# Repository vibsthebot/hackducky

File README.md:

# HackDucky - New YSWS!

The hackclub themed USB rubber ducky ! - Check out [hackducky](https://hackclub.slack.com/archives/C08B8HZBC85)

# What is this?

Hackducky is hackclubs own version of making a USB rubber ducky built by hackclubers.A usb rubber ducky is basically something that looks like a USB but is actually a trojan. It pretends to be a keyboard to the computer allowing you to basically take control of the computer you plug it into

## What you get

- Hackducky Board
    -  Dual USB ports (USB-A and USB-C)
    -  LED for the status - you can use it for other things if you like !
    -  Button for any extra features you may want to add !
    -  All duckyscripts are stored in the Hackduckys flash memory !

## Getting Started

1. - WIP

# Submission Criteria  

## 1. Time Requirement  
- **HackDucky Light:** Minimum of **3-4 hours** of development.  
- **HackDucky Pro:** Minimum of **5-6 hours** of development.  
- **Tracking:** Use **WakaTime** to track your development hours.  

## 2. Core Features (Must have 3)  
- Not just simple actions—core features should be impactful and unique.  
- **Examples:**  
  1. Open Notepad, start typing gibberish, and change the desktop background.  
  2. Open the terminal, run commands, and create pop-ups to scare the user.  
  3. Fake a system crash by downloading a **blue screen image** and freezing the mouse.  

## 3. Additional Features (Must have 5-7)  
- Include **at least 5-7 normal features** outside of the core features.  
- The more features, the better!  

## 4. Originality  
- Your project must be an **original idea** and not a direct copy from a tutorial.  
- Tutorials can be referenced, but your submission should be your own creation.  

## 5. Submission Limit  
- You can submit **multiple projects**, but you can only receive **one HackDucky** (either Pro or Light).  

## What the LED indicators mean

- Triple blink: Startup Sequence
- Single blink: Working/Processing - running/Starting Execution
- Rapid blinking: DuckyScript is incorrect / Firmware broke 😭 - Create a PR or new issue desribing the firmware problem

## Troubleshooting the LED's

1. LED rapidly blinking at startup:
 - Programming Mode
    - All is working great!
    - Its meant to blink rapidly in this mode
 - Payload Mode
       - Something is wrong with your duckyscript
       - Something is wrong with the firmware ( Create an Issue! )

3. Script not running:
   - Check script syntax
   - Verify file is properly saved
   - Try reformatting MicroSD card

4. Keyboard not recognized:
   - Try different USB port
   - Check USB connection
   - Verify target system supports USB HID

## Safety Notes

- pls dont hack people with this pls - its only ethical

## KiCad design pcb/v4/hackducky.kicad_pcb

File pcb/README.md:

# 🦆 HackDucky

HackDucky is a compact, powerful RP2040-based USB device inspired by the concept of a "USB Rubber Ducky" — but fully open-source and customizable. It features dual USB ports (Type-A & Type-C), RGB status indicator, SD card support, and a generous 16MB flash. Ideal for scripting, automation, HID emulation, and more!

## 🔧 Features

* **RP2040 Microcontroller** – Dual-core Arm Cortex-M0+ @ 133MHz
* **16MB Flash** – Plenty of room for Ducky scripts, firmware, and more
* **USB-C & USB-A Ports** – Plug into any host device with ease
* **Micro SD Card Slot** – Store payloads, logs, or configs externally
* **RGB Neopixel** – Visual feedback for status, payload execution, etc
* **Compact Custom PCB** – Designed with portability and DIY hacking in mind

## 🧠 What Can It Do?

* Act as a USB HID device (keyboard/mouse automation)
* Emulate serial or mass storage devices
* Read payloads from SD card and execute them
* Light up RGB based on execution state (idle, running, error)
* Load firmware like CircuitPython, TinyUSB, or custom UF2 payloads

## 💻 Getting Started

1. **Flash Firmware**
   Connect via USB and flash with your favorite firmware (e.g. CircuitPython, Raspberry Pi Pico SDK UF2, etc).

2. **Insert SD Card (Optional)**
   Load your payloads/scripts/configs on a FAT32-formatted card.

3. **Connect to Host via USB-A**
   HackDucky will start executing its payload or HID script automatically (depending on firmware).

4. **RGB Status LED**

## ⚡ Power & USB Notes

* Use **USB-C & USB-A for power and flashing**

## 🧰 Tools Used

* KiCad for PCB Design
* RP2040 SDK / CircuitPython
* Open-source hardware and firmware philosophy

## 📸 Preview
Coming Soon
## 🔐 Disclaimer

This device is for **educational and ethical hacking purposes only**. Use responsibly. The creators is not responsible for any misuse.

---

## 📫 Connect

Built with ❤️ by [Souptik Samanta](https://souptik.me) & [Aarav Jhamb](https://github.com/The-UnknownHacker)

GitHub: [@souptik-samanta](https://github.com/souptik-samanta) & [Aarav Jhamb](https://github.com/The-UnknownHacker)
Instagram: [@souptik.me](https://instagram.com/souptik.me) & [Aarav Jhamb](aaravjhamb.com)
Hack Clubber & Hardware Hacker 💻🔌             Hack Clubber & Ethical Hacker 💻🔌

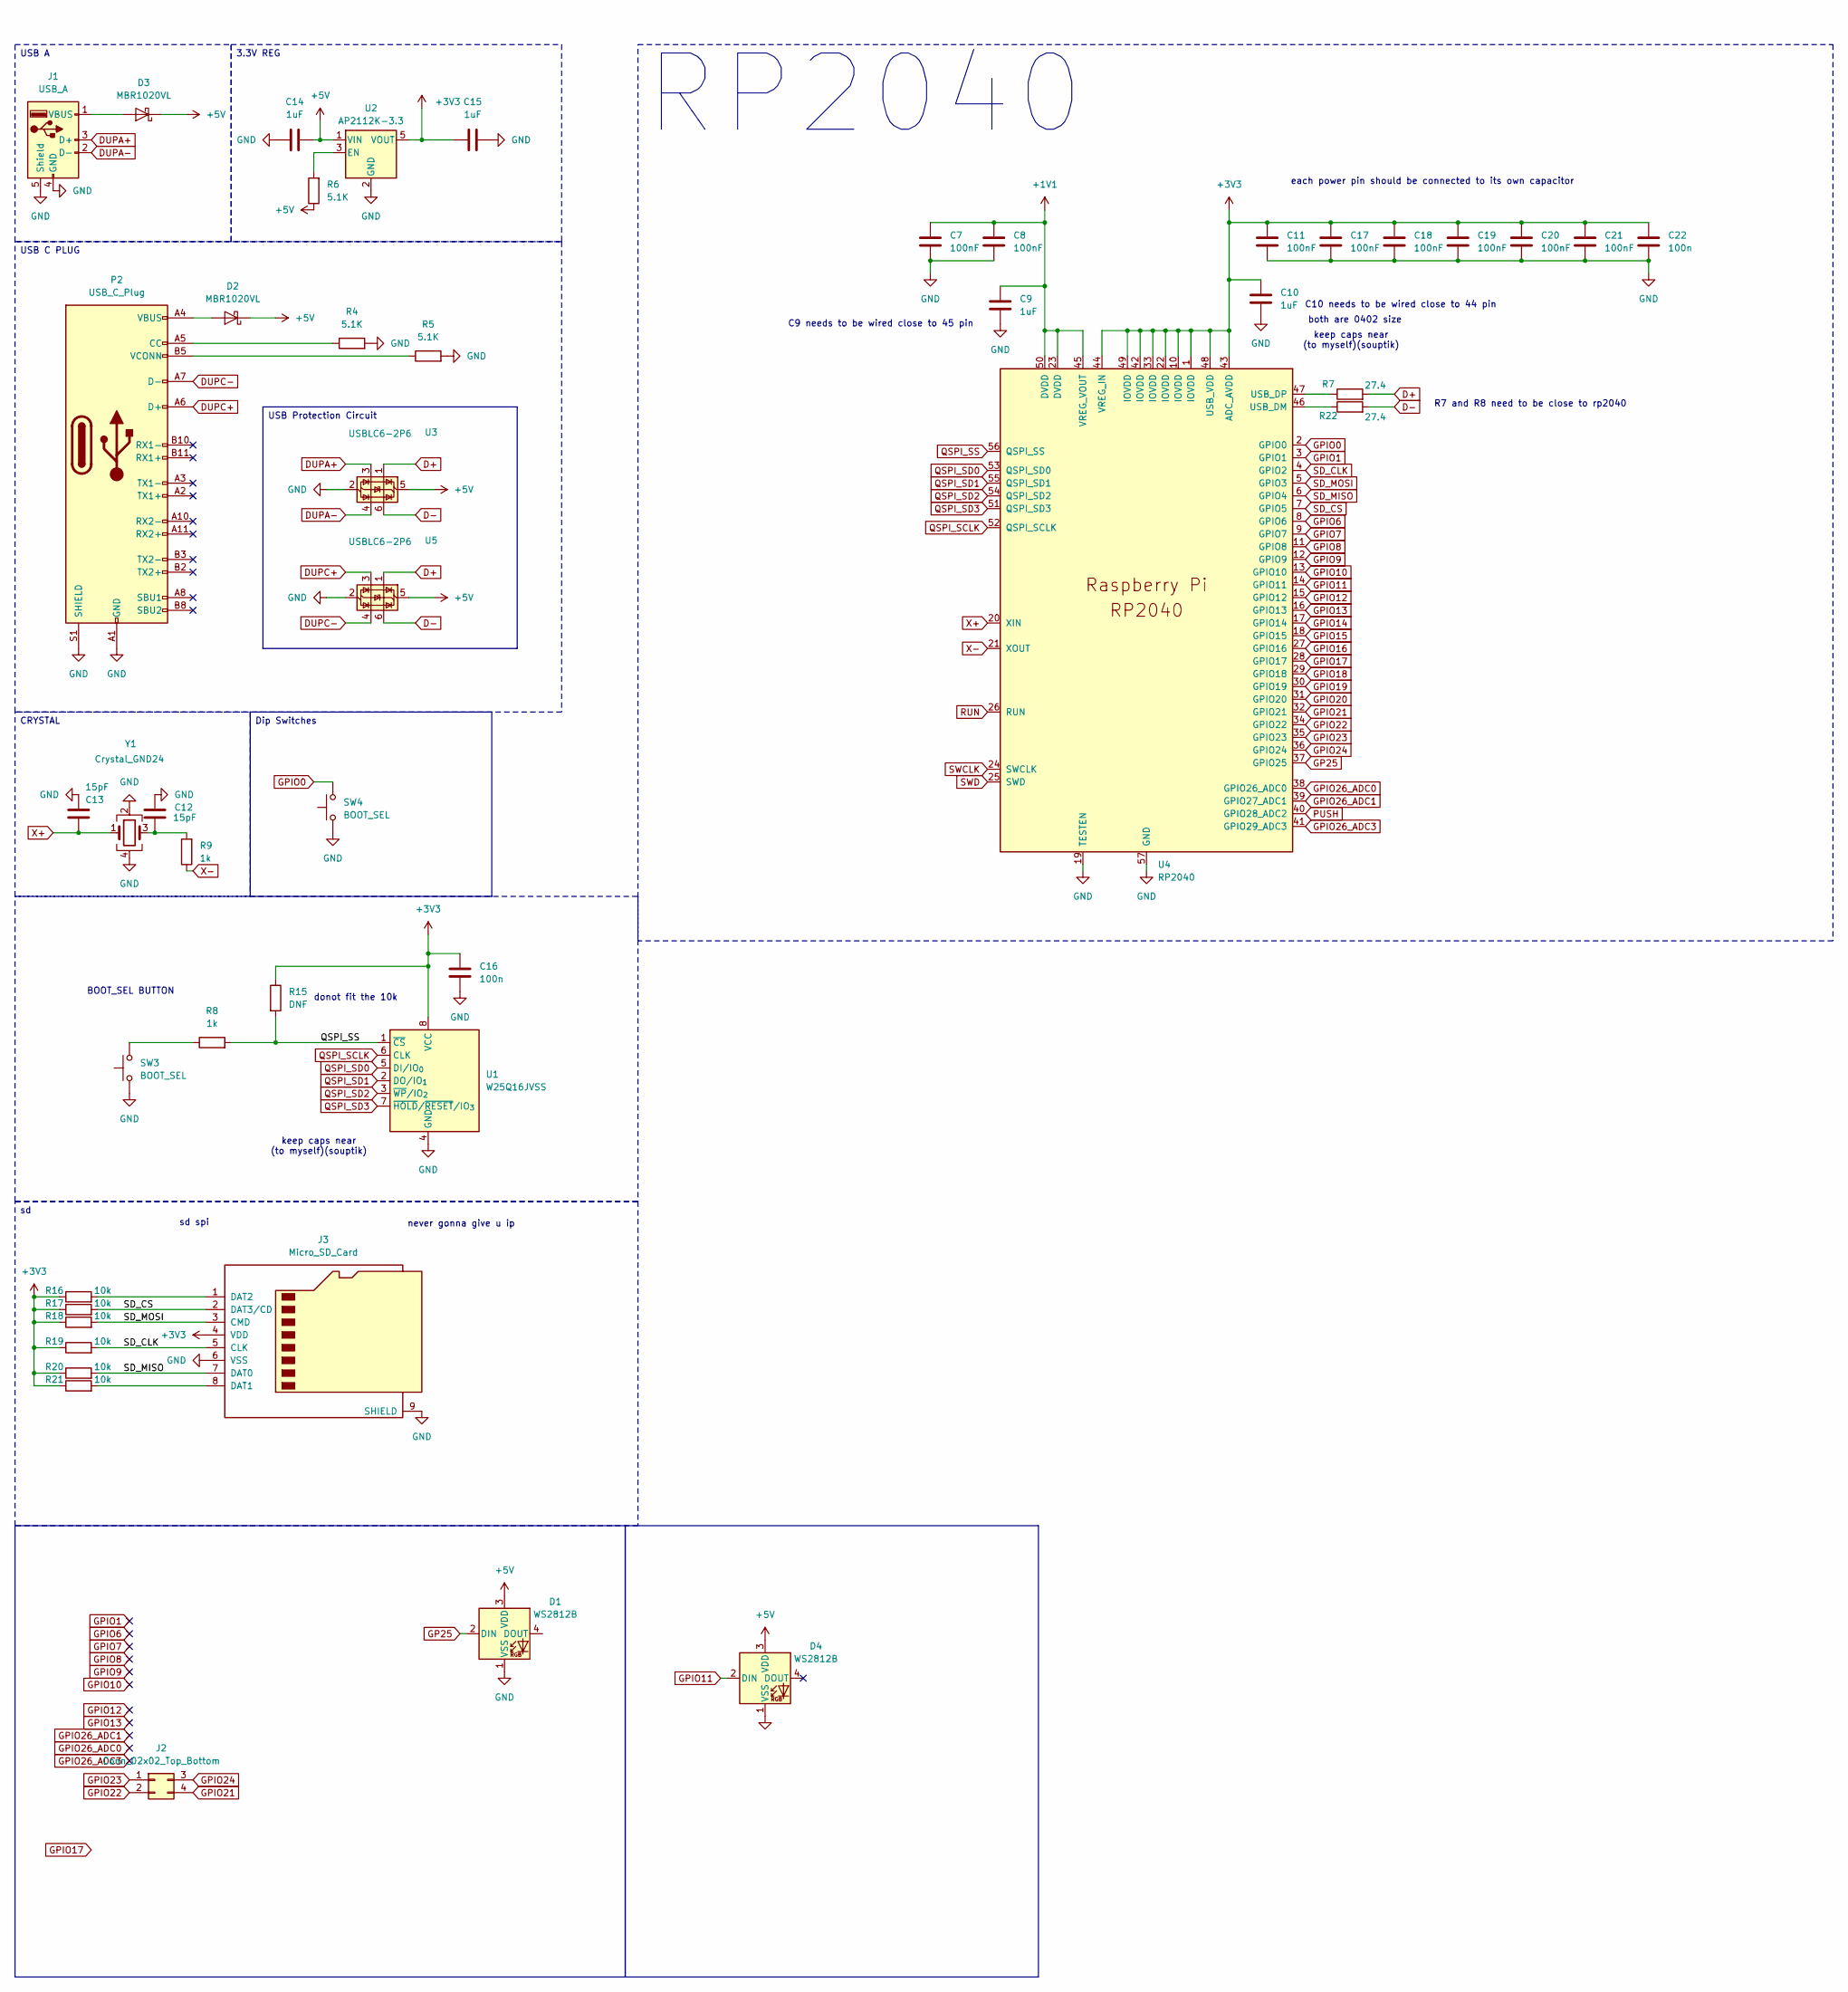
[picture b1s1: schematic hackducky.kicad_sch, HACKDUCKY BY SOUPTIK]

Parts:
C7, C8, C11, C17, C18, C19, C20, C21: 100nF; C_0402_1005Metric
C9, C10, C14: 1uF; C_0402_1005Metric
C12, C13: 15pF; C_0402_1005Metric
C15: 1uF; C_0805_2012Metric
C16, C22: 100n; C_0402_1005Metric
D1, D4: WS2812B; LED_WS2812B-2020_PLCC4_2.0x2.0mm
D2, D3: MBR1020VL; D_SOD-123F
J1: USB_A; USB_A_CNCTech_1001-011-01101_Horizontal
J2: Conn_02x02_Top_Bottom; PinHeader_2x02_P1.00mm_Vertical_SMD
J3: Micro_SD_Card; microSD_HC_Molex_47219-2001
P2: USB_C_Plug; USB_C_Plug_Molex_105444
R4, R5: 5.1K; C_0402_1005Metric
R6: 5.1K; R_0805_2012Metric
R7, R22: 27.4; R_0402_1005Metric
R8, R9: 1k; R_0402_1005Metric
R15: DNF; R_0805_2012Metric_Pad1.20x1.40mm_HandSolder
R16, R17, R18, R19, R20, R21: 10k; R_0402_1005Metric
SW3, SW4: BOOT_SEL; SW_Push_SPST_NO_Alps_SKRK; LCSC C318884
U1: W25Q16JVSS; SOIC-8_5.3x5.3mm_P1.27mm
U2: AP2112K-3.3; SOT-23-5
U3, U5: USBLC6-2P6; SOT-666
U4: RP2040; QFN-56-1EP_7x7mm_P0.4mm_EP3.2x3.2mm
Y1: Crystal_GND24; Crystal_SMD_Abracon_ABM8G-4Pin_3.2x2.5mm

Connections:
+1V1: C7.1, C8.1, C9.1, U4.23 (DVDD), U4.45 (VREG_VOUT), U4.50 (DVDD)
+3V3: C10.1, C11.1, C15.2, C16.1, C17.1, C18.1, C19.1, C20.1, C21.1, C22.1, J3.4 (VDD), R15.1, R16.1, R17.1, R18.1, R19.1, R20.1, R21.1, U1.8 (VCC), U2.5 (VOUT), U4.1 (IOVDD), U4.10 (IOVDD), U4.22 (IOVDD), U4.33 (IOVDD), U4.42 (IOVDD), U4.43 (ADC_AVDD), U4.44 (VREG_IN), U4.48 (USB_VDD), U4.49 (IOVDD)
+5V: C14.1, D1.3 (VDD), D2.1 (K), D3.1 (K), D4.3 (VDD), R6.1, U2.1 (VIN), U3.5 (VBUS), U5.5 (VBUS)
D+: R7.2, U3.1 (I/O1), U5.1 (I/O1)
D-: R22.2, U3.6 (I/O1), U5.6 (I/O1)
DUPA+: J1.3 (D+), U3.3 (I/O2)
DUPA-: J1.2 (D-), U3.4 (I/O2)
DUPC+: P2.A6 (D+), U5.3 (I/O2)
DUPC-: P2.A7 (D-), U5.4 (I/O2)
GND: C7.2, C8.2, C9.2, C10.2, C11.2, C12.2, C13.2, C14.2, C15.1, C16.2, C17.2, C18.2, C19.2, C20.2, C21.2, C22.2, D1.1 (VSS), D4.1 (VSS), J1.4 (GND), J1.5 (Shield), J3.6 (VSS), J3.9 (SHIELD), P2.A1 (GND), P2.A12 (GND), P2.B1 (GND), P2.B12 (GND), P2.S1 (SHIELD), R4.2, R5.2, SW3.1, SW4.1, U1.4 (GND), U2.2 (GND), U3.2 (GND), U4.19 (TESTEN), U4.57 (GND), U5.2 (GND), Y1.2, Y1.4
GP25: D1.2 (DIN), U4.37 (GPIO25)
GPIO0: SW4.2, U4.2 (GPIO0)
GPIO1: U4.3 (GPIO1)
GPIO6: U4.8 (GPIO6)
GPIO7: U4.9 (GPIO7)
GPIO8: U4.11 (GPIO8)
GPIO9: U4.12 (GPIO9)
GPIO10: U4.13 (GPIO10)
GPIO11: D4.2 (DIN), U4.14 (GPIO11)
GPIO12: U4.15 (GPIO12)
GPIO13: U4.16 (GPIO13)
GPIO14: U4.17 (GPIO14)
GPIO15: U4.18 (GPIO15)
GPIO16: U4.27 (GPIO16)
GPIO17: U4.28 (GPIO17)
GPIO18: U4.29 (GPIO18)
GPIO19: U4.30 (GPIO19)
GPIO20: U4.31 (GPIO20)
GPIO21: J2.4, U4.32 (GPIO21)
GPIO22: J2.2, U4.34 (GPIO22)
GPIO23: J2.1, U4.35 (GPIO23)
GPIO24: J2.3, U4.36 (GPIO24)
GPIO26_ADC0: U4.38 (GPIO26_ADC0)
GPIO26_ADC1: U4.39 (GPIO27_ADC1)
GPIO26_ADC3: U4.41 (GPIO29_ADC3)
unnamed: C12.1, R9.2, Y1.3
unnamed: D2.2 (A), P2.A4 (VBUS), P2.A9 (VBUS), P2.B4 (VBUS), P2.B9 (VBUS)
unnamed: D3.2 (A), J1.1 (VBUS)
unnamed: J3.8 (DAT1), R21.2
unnamed: J3.1 (DAT2), R16.2
unnamed: P2.A5 (CC), R4.1
unnamed: P2.B5 (VCONN), R5.1
unnamed: R8.1, SW3.2
unnamed: R6.2, U2.3 (EN)
unnamed: R22.1, U4.46 (USB_DM)
unnamed: R7.1, U4.47 (USB_DP)
PUSH: U4.40 (GPIO28_ADC2)
QSPI_SCLK: U1.6 (CLK), U4.52 (QSPI_SCLK)
QSPI_SD0: U1.5 (DI/IO_{0}), U4.53 (QSPI_SD0)
QSPI_SD1: U1.2 (DO/IO_{1}), U4.55 (QSPI_SD1)
QSPI_SD2: U1.3 (~WP/IO_{2}), U4.54 (QSPI_SD2)
QSPI_SD3: U1.7 (~HOLD/~RESET/IO_{3}), U4.51 (QSPI_SD3)
QSPI_SS: R8.2, R15.2, U1.1 (~CS), U4.56 (QSPI_SS)
RUN: U4.26 (RUN)
SD_CLK: J3.5 (CLK), R19.2, U4.4 (GPIO2)
SD_CS: J3.2 (DAT3/CD), R17.2, U4.7 (GPIO5)
SD_MISO: J3.7 (DAT0), R20.2, U4.6 (GPIO4)
SD_MOSI: J3.3 (CMD), R18.2, U4.5 (GPIO3)
SWCLK: U4.24 (SWCLK)
SWD: U4.25 (SWD)
X+: C13.1, U4.20 (XIN), Y1.1
X-: R9.1, U4.21 (XOUT)

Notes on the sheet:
sd spi
C9 needs to be wired close to 45 pin
keep caps near (to myself)(souptik)
donot fit the 10k
R7 and R8 need to be close to rp2040
C10 needs to be wired close to 44 pin
BOOT_SEL BUTTON
never gonna give u ip
both are 0402 size
each power pin should be connected to its own capacitor
CRYSTAL
RP2040
USB Protection Circuit
USB C PLUG
Dip Switches
3.3V REG
USB A

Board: 2 copper layers, 46 parts (0 on the bottom side), 40 nets, no tracks yet.

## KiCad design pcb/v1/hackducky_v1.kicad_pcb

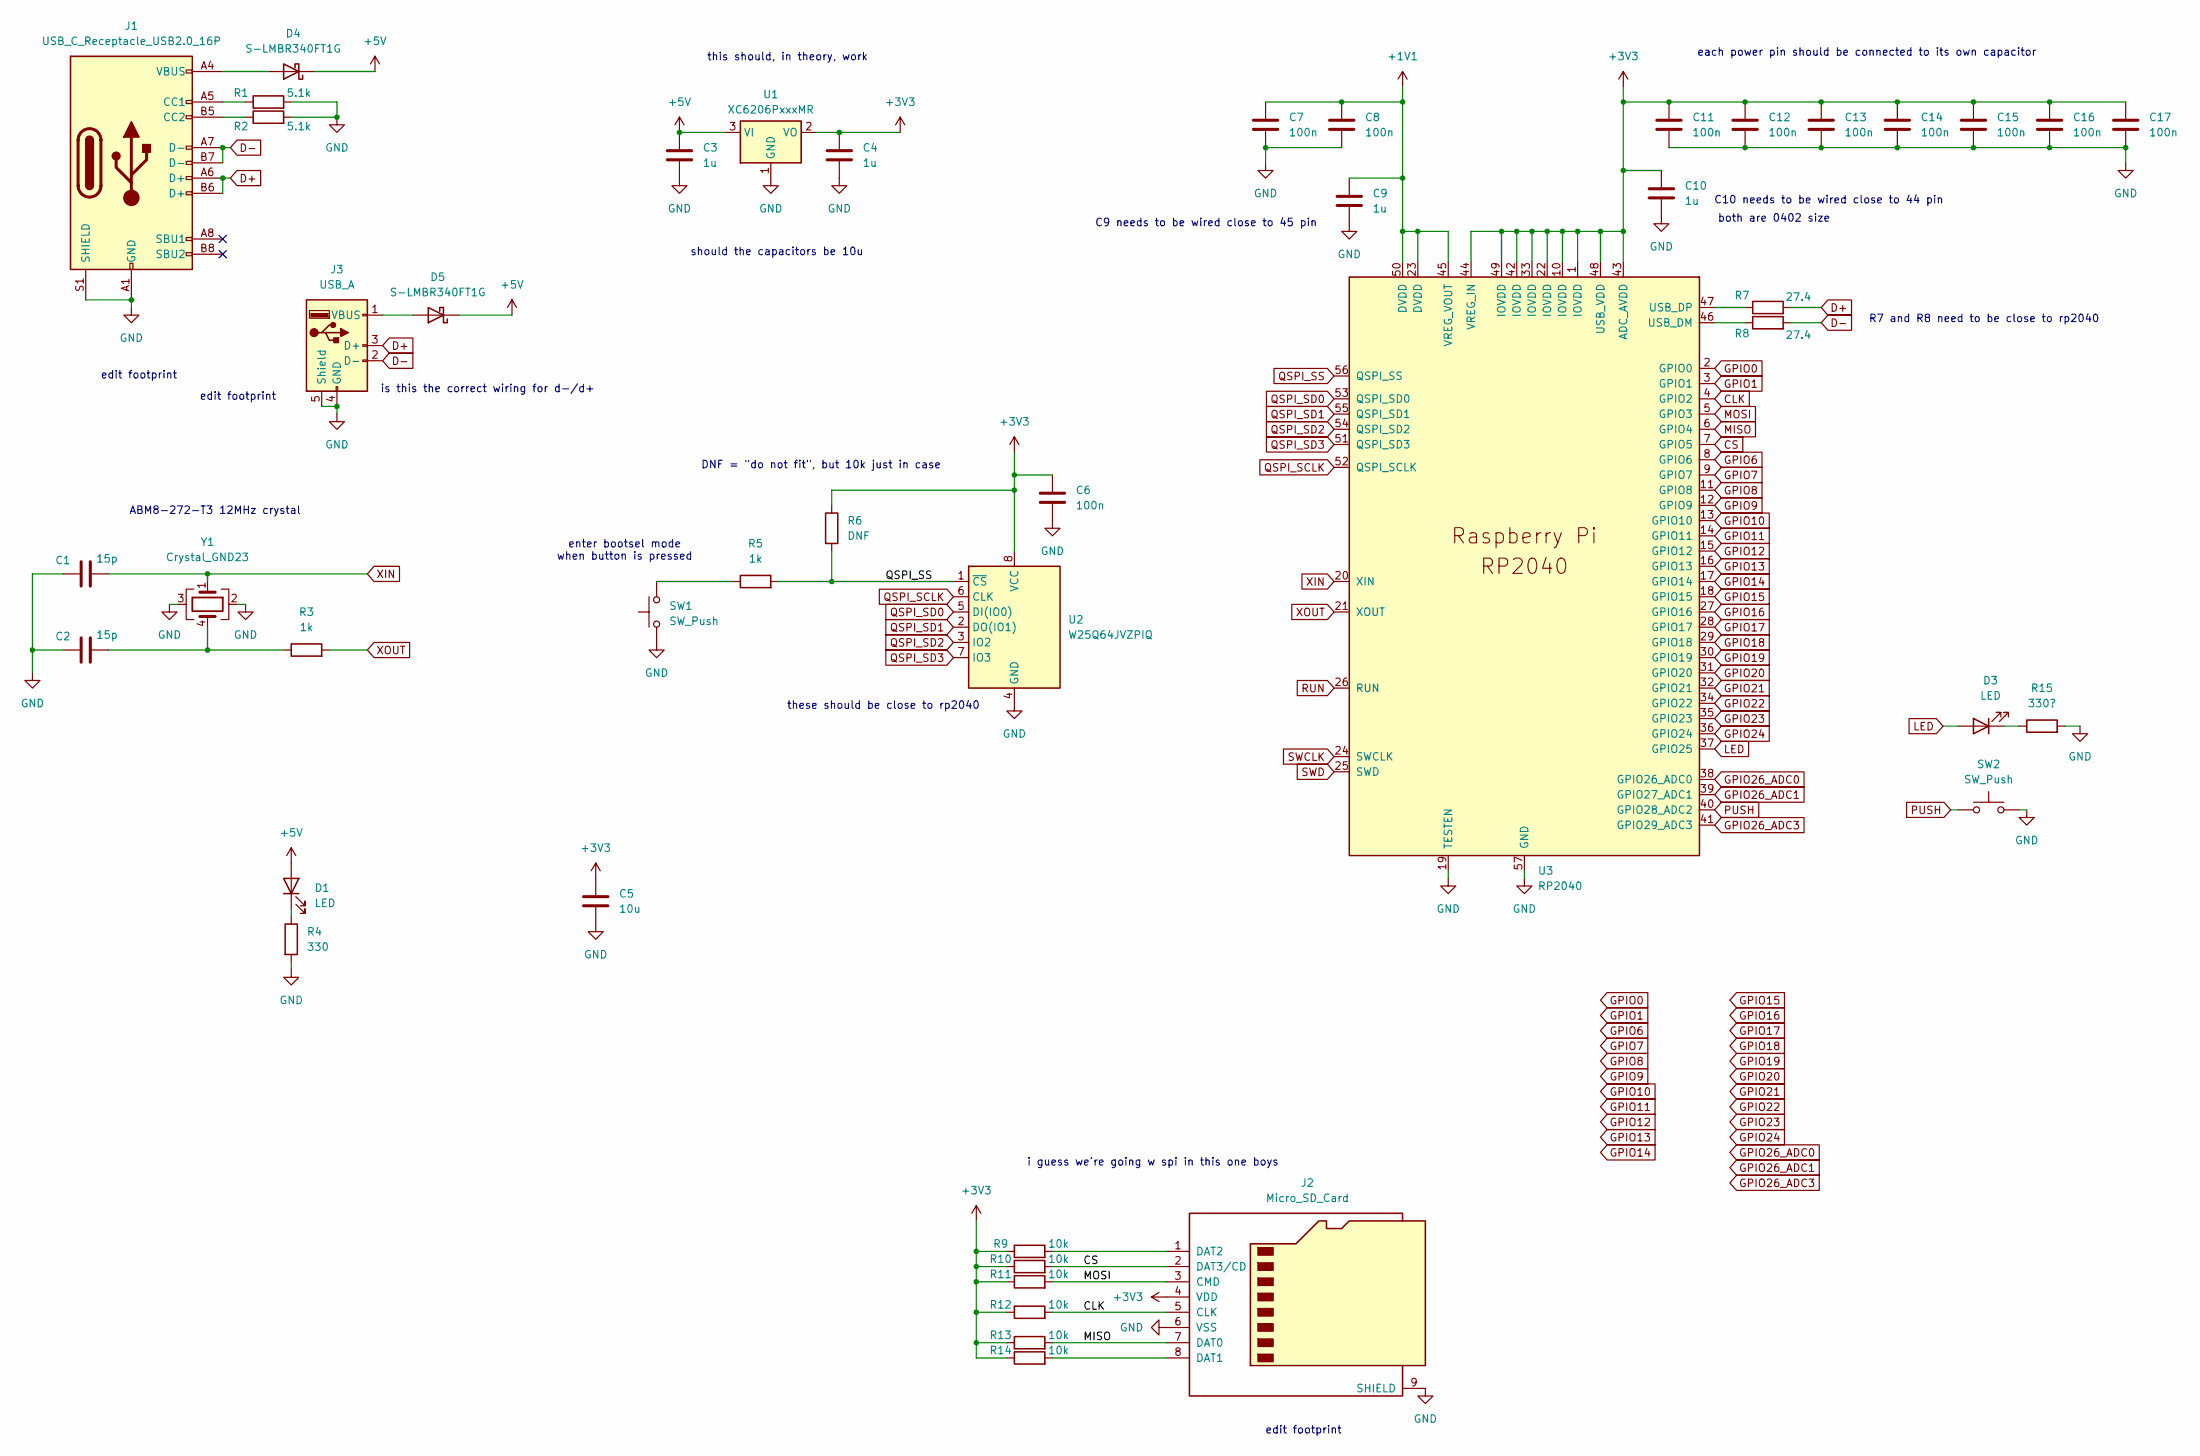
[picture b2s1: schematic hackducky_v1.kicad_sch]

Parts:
C1, C2: 15p; C_0402_1005Metric
C3, C4, C9, C10: 1u; C_0402_1005Metric
C5: 10u; C_0402_1005Metric
C6, C7, C8, C11, C12, C13, C14, C15, C16, C17: 100n; C_0402_1005Metric
D1: LED; LED_0805_2012Metric
D3: LED; LED_0402_1005Metric
D4, D5: S-LMBR340FT1G; D_0805_2012Metric
J1: USB_C_Receptacle_USB2.0_16P; USB_C_Plug_Molex_105444
J2: Micro_SD_Card; microSD_HC_Molex_47219-2001
J3: USB_A; USB3_A_Plug_Wuerth_692112030100_Horizontal
R1, R2: 5.1k; R_0402_1005Metric
R3, R5: 1k; R_0402_1005Metric
R4: 330; R_0402_1005Metric
R6: DNF; R_0402_1005Metric
R7, R8: 27.4; R_0402_1005Metric
R9, R10, R11, R12, R13, R14: 10k; R_0402_1005Metric
R15: 330?; R_0402_1005Metric
SW1: SW_Push; SW_Push_1P1T_XKB_TS-1187A; LCSC C318884
SW2: SW_Push; SW_PUSH_6mm
U1: XC6206PxxxMR; SOT-23-3
U2: W25Q64JVZPIQ; WSON-8-1EP_6x5mm_P1.27mm_EP3.4x4mm
U3: RP2040; QFN-56-1EP_7x7mm_P0.4mm_EP3.2x3.2mm
Y1: Crystal_GND23; Crystal_SMD_Abracon_ABM8G-4Pin_3.2x2.5mm

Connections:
+1V1: C7.1, C8.1, C9.1, U3.23 (DVDD), U3.45 (VREG_VOUT), U3.50 (DVDD)
+3V3: C4.1, C5.1, C6.1, C10.1, C11.1, C12.1, C13.1, C14.1, C15.1, C16.1, C17.1, J2.4 (VDD), R6.1, R9.1, R10.1, R11.1, R12.1, R13.1, R14.1, U1.2 (VO), U2.8 (VCC), U3.1 (IOVDD), U3.10 (IOVDD), U3.22 (IOVDD), U3.33 (IOVDD), U3.42 (IOVDD), U3.43 (ADC_AVDD), U3.44 (VREG_IN), U3.48 (USB_VDD), U3.49 (IOVDD)
+5V: C3.1, D1.2 (A), D4.1 (K), D5.1 (K), U1.3 (VI)
CLK: J2.5 (CLK), R12.2, U3.4 (GPIO2)
CS: J2.2 (DAT3/CD), R10.2, U3.7 (GPIO5)
D+: J1.A6 (D+), J1.B6 (D+), J3.3 (D+), R7.2
D-: J1.A7 (D-), J1.B7 (D-), J3.2 (D-), R8.2
GND: C1.1, C2.1, C3.2, C4.2, C5.2, C6.2, C7.2, C8.2, C9.2, C10.2, C11.2, C12.2, C13.2, C14.2, C15.2, C16.2, C17.2, J1.A1 (GND), J1.A12 (GND), J1.B1 (GND), J1.B12 (GND), J1.S1 (SHIELD), J2.6 (VSS), J2.9 (SHIELD), J3.4 (GND), J3.5 (Shield), R1.2, R2.2, R4.2, R15.2, SW1.1, SW2.2, U1.1 (GND), U2.4 (GND), U3.19 (TESTEN), U3.57 (GND), Y1.2, Y1.3
GPIO0: U3.2 (GPIO0)
GPIO1: U3.3 (GPIO1)
GPIO6: U3.8 (GPIO6)
GPIO7: U3.9 (GPIO7)
GPIO8: U3.11 (GPIO8)
GPIO9: U3.12 (GPIO9)
GPIO10: U3.13 (GPIO10)
GPIO11: U3.14 (GPIO11)
GPIO12: U3.15 (GPIO12)
GPIO13: U3.16 (GPIO13)
GPIO14: U3.17 (GPIO14)
GPIO15: U3.18 (GPIO15)
GPIO16: U3.27 (GPIO16)
GPIO17: U3.28 (GPIO17)
GPIO18: U3.29 (GPIO18)
GPIO19: U3.30 (GPIO19)
GPIO20: U3.31 (GPIO20)
GPIO21: U3.32 (GPIO21)
GPIO22: U3.34 (GPIO22)
GPIO23: U3.35 (GPIO23)
GPIO24: U3.36 (GPIO24)
GPIO26_ADC0: U3.38 (GPIO26_ADC0)
GPIO26_ADC1: U3.39 (GPIO27_ADC1)
GPIO26_ADC3: U3.41 (GPIO29_ADC3)
LED: D3.2 (A), U3.37 (GPIO25)
MISO: J2.7 (DAT0), R13.2, U3.6 (GPIO4)
MOSI: J2.3 (CMD), R11.2, U3.5 (GPIO3)
unnamed: C2.2, R3.1, Y1.4
unnamed: D1.1 (K), R4.1
unnamed: D3.1 (K), R15.1
unnamed: D4.2 (A), J1.A4 (VBUS), J1.A9 (VBUS), J1.B4 (VBUS), J1.B9 (VBUS)
unnamed: D5.2 (A), J3.1 (VBUS)
unnamed: J1.A5 (CC1), R1.1
unnamed: J1.B5 (CC2), R2.1
unnamed: J2.8 (DAT1), R14.2
unnamed: J2.1 (DAT2), R9.2
unnamed: R5.1, SW1.2
unnamed: R8.1, U3.46 (USB_DM)
unnamed: R7.1, U3.47 (USB_DP)
PUSH: SW2.1, U3.40 (GPIO28_ADC2)
QSPI_SCLK: U2.6 (CLK), U3.52 (QSPI_SCLK)
QSPI_SD0: U2.5 (DI(IO0)), U3.53 (QSPI_SD0)
QSPI_SD1: U2.2 (DO(IO1)), U3.55 (QSPI_SD1)
QSPI_SD2: U2.3 (IO2), U3.54 (QSPI_SD2)
QSPI_SD3: U2.7 (IO3), U3.51 (QSPI_SD3)
QSPI_SS: R5.2, R6.2, U2.1 (~CS), U3.56 (QSPI_SS)
RUN: U3.26 (RUN)
SWCLK: U3.24 (SWCLK)
SWD: U3.25 (SWD)
XIN: C1.2, U3.20 (XIN), Y1.1
XOUT: R3.2, U3.21 (XOUT)

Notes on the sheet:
these should be close to rp2040
C9 needs to be wired close to 45 pin
is this the correct wiring for d-/d+
R7 and R8 need to be close to rp2040
this should, in theory, work
C10 needs to be wired close to 44 pin
should the capacitors be 10u
i guess we're going w spi in this one boys
both are 0402 size
edit footprint
each power pin should be connected to its own capacitor
enter bootsel mode when button is pressed
ABM8-272-T3 12MHz crystal
DNF = "do not fit", but 10k just in case

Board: 2 copper layers, 45 parts (0 on the bottom side), 32 nets, no tracks yet.

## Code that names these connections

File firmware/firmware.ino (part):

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#include <vector>
#include <map>

#define SD_CS_PIN   5    
#define SD_SCK_PIN  2    
#define SD_MOSI_PIN 3    
#define SD_MISO_PIN 4    

#define LED_PIN     25   

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void setup() {
  pinMode(LED_PIN, OUTPUT);
  pinMode(BUTTON_PIN, INPUT_PULLUP);
  SPI.setRX(SD_MISO_PIN);
  SPI.setTX(SD_MOSI_PIN);
  SPI.setSCK(SD_SCK_PIN);
  
  if (!usb_hid1.begin() || !usb_hid2.begin()) {
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  usb_hid1.setPollInterval(1);
  usb_hid2.setPollInterval(1);
  
  if (!SD.begin(SD_CS_PIN)) {
    while(1) {
      digitalWrite(LED_PIN, HIGH);
      delay(100);
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    kbState.currentMode = USB_MODE_STORAGE;
    usb_hid1.end();
    usb_hid2.end();
    if (!SD.begin(SD_CS_PIN)) {
      Serial.println("Storage mode failed!");
      return;
    }
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    usb_hid2.begin();
    usb_hid1.setPollInterval(1);
    usb_hid2.setPollInterval(1);
    if (!SD.begin(SD_CS_PIN)) {
      Serial.println("Storage mode failed!");
      return;
    }
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
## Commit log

2025-02-03 add pcb folder + files
2025-02-04 Create and Upload the Base Firmware
2025-02-04 Update firmware to be Fully compatible with Ducky script
2025-02-04 Add submission criteria
2025-02-05 add v1 wip
2025-02-06 updated schematic, started pcb
2025-02-06 Added site directory
2025-02-06 Upload Hackducky Site v1
2025-02-06 Added site as a normal directory
2025-02-06 i hate how macos makes random files
2025-02-07 Fix NextJS
2025-02-07 Fix Issues with NextJS Compiling
2025-02-08 FINAL fixes for nextjs
2025-02-08 Update tutorial and Fix Vercel config
2025-02-09 no buzzer
2025-02-16 Update the horrible firmware to Circuit Python !
2025-02-18 Finish the firmware by adding the programming mode and bug fixes
2025-02-18 add: support for layouts
2025-02-20 Update README.md to match new firmware
2025-02-20 Update README.md to match hardware changes
2025-03-03 Update tutorial.md with better wording
2025-03-04 added the DEFAULT_DELAY command to set the time between commands
2025-03-11 Make tutorial text move more quickly!
2025-04-20 soupy soupy v3
2025-04-23 PCB Done 🥳
2025-06-28 Add v7 of the PCB 💀
2025-06-28 Add my submission
2025-06-28 Update to new site
2025-06-29 add .gitignore
2025-07-05 Just got firmware working by fixing some libraries
2025-07-06 added all commands except control and alt
2025-07-07 added a potentially working recursive function to make commands with multiple commands easier.
